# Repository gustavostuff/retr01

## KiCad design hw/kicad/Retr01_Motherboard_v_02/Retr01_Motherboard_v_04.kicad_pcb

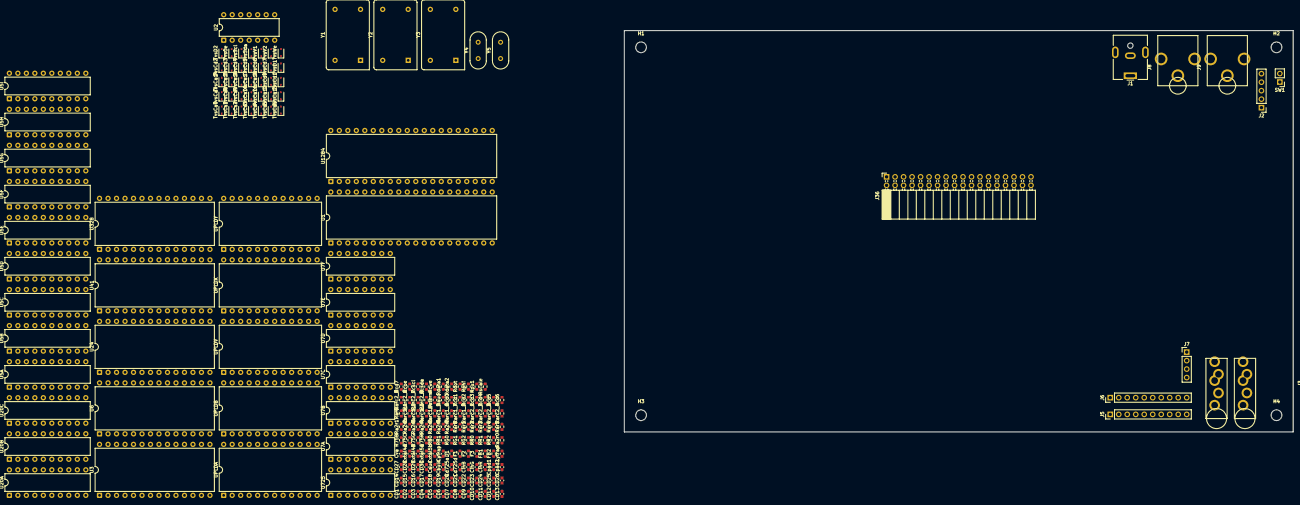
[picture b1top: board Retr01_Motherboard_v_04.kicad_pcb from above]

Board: 4 copper layers, 200.0 x 120.0 mm, 202 parts (0 on the bottom side), 213 nets, no tracks yet.

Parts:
CD1, CD2, CD3, CD4, CD5, CD6, CD7, CD8, CD9, CD10, CD11, CD12, CD13, CD14, CD15, CD16, CD17, CD18, CD19, CD20, CD21, CD22, CD23, CD24, CD25, CD26, CD27, CD28, CD29, CD30: C_100N; C_0603_1608Metric
Caud: C_10U_AUD; C_0603_1608Metric
Cbulk: C_BULK; C_0603_1608Metric
Cd725a, Cd725d: C_100N; C_0603_1608Metric
CinB: C_100N; C_0603_1608Metric
CinG: C_100N; C_0603_1608Metric
CinR: C_100N; C_0603_1608Metric
Cpad1, Cpad2: C_100N; C_0603_1608Metric
Cva: C_10U; C_0603_1608Metric
Cxtal4a, Cxtal4b, Cxtal5a, Cxtal5b: C_22P; C_0603_1608Metric
Cytrap: C_100N; C_0603_1608Metric
D1: SCHOTTKY; R_0603_1608Metric
F1, F2, F3: PPTC; R_0603_1608Metric
FB1, FB2: FERRITE; R_0603_1608Metric
H1, H2, H3, H4: MountingHole_3.2mm_M3
J1: BARREL_5V; BarrelJack_CUI_PJ-063AH_Horizontal
J2: RGBS_HDR; PinHeader_1x05_P2.54mm_Vertical
J3: TRS_P1; Jack_3.5mm_Switchcraft_35RAPC2BVN4_Vertical
J4: TRS_P2; Jack_3.5mm_Switchcraft_35RAPC2BVN4_Vertical
J5: ARCADE_P1; PinHeader_1x10_P2.54mm_Vertical
J6: ARCADE_P2; PinHeader_1x10_P2.54mm_Vertical
J7: CAB_PWR_RST; PinHeader_1x04_P2.54mm_Vertical
J8: AUDIO_OUT; CUI_RCJ-01x_Vertical
J9: COMPOSITE_OUT; CUI_RCJ-01x_Vertical
J36: CART_EDGE_36; PinSocket_2x18_P2.54mm_Horizontal
Lytrap: L_YTRAP; L_0603_1608Metric
R75B, R75C, R75G, R75R: R_75; R_0603_1608Metric
RB0: R_2K; R_0603_1608Metric
RB1: R_1K; R_0603_1608Metric
RG0: R_4K; R_0603_1608Metric
RG1: R_2K; R_0603_1608Metric
RG2: R_1K; R_0603_1608Metric
RR0: R_4K; R_0603_1608Metric
RR1: R_2K; R_0603_1608Metric
RR2: R_1K; R_0603_1608Metric
Ra2r0, Ra2r1, Ra2r2, Ra2r3, Ra2r4, Ra2r5, Ra2r6, Ra2r7: R_20K; R_0603_1608Metric
Rar0, Rar1, Rar2, Rar3, Rar4, Rar5, Rar6: R_10K; R_0603_1608Metric
Rarc1_1, Rarc1_2, Rarc1_3, Rarc1_4, Rarc1_5, Rarc1_6, Rarc1_7, Rarc1_8, Rarc2_1, Rarc2_2, Rarc2_3, Rarc2_4, Rarc2_5, Rarc2_6, Rarc2_7, Rarc2_8: R_47; R_0603_1608Metric
Raterm: R_20K; R_0603_1608Metric
Raud: R_1K; R_0603_1608Metric
Rcd0, Rcd1, Rcd2, Rcd3, Rcd4, Rcd5, Rcd6, Rcd7: R_33; R_0603_1608Metric
Rcoe: R_33; R_0603_1608Metric
Rcscl: R_33; R_0603_1608Metric
Rcsda: R_33; R_0603_1608Metric
Rcwe: R_33; R_0603_1608Metric
Rdata1, Rdata2: R_47; R_0603_1608Metric
Rdot: R_33; R_0603_1608Metric
Rphi: R_33; R_0603_1608Metric
Rpu1: R_4K7; R_0603_1608Metric
Rscale: R_10K; R_0603_1608Metric
SW1: SCALE_SW; PinHeader_1x02_P2.54mm_Vertical
TvsCa0, TvsCa1, TvsCa2, TvsCa3, TvsCa4, TvsCa5, TvsCa6, TvsCa7, TvsCa8, TvsCa9, TvsCa10, TvsCa11, TvsCa12, TvsCa13, TvsCa14, TvsCa15, TvsCa16, TvsCa17, TvsCa18: TVS_5V; D_SOD-323
TvsCd0, TvsCd1, TvsCd2, TvsCd3, TvsCd4, TvsCd5, TvsCd6, TvsCd7: TVS_5V; D_SOD-323
TvsD1, TvsD2: TVS_5V; D_SOD-323
TvsOe: TVS_5V; D_SOD-323
TvsScl: TVS_5V; D_SOD-323
TvsSda: TVS_5V; D_SOD-323
TvsV1, TvsV2: TVS_5V; D_SOD-323
TvsWe: TVS_5V; D_SOD-323
U1: W65C02S; DIP-40_W15.24mm
U2: SN74HC14; DIP-14_W7.62mm
U3, U6, U41: AS6C62256; DIP-28_W15.24mm
U5A, U5B, U5C, U5D, U5E, U5F, U5G, U5H, U5I: SN74HC573; DIP-20_W7.62mm
U7A, U7B, U7C, U7D, U7E, U7F: SN74HC157; DIP-16_W7.62mm
U20A, U20B, U20C: SN74HC245; DIP-20_W7.62mm
U24: AT27C256R; DIP-28_W15.24mm
U328: ATmega328P; DIP-28_W15.24mm
U725: AD725; DIP-16_W7.62mm
U1284: ATmega1284P; DIP-40_W15.24mm
UPLDA: ATF22V10; DIP-24_W15.24mm
UPLDB: ATF22V10; DIP-24_W15.24mm
UPLDV: ATF22V10; DIP-24_W15.24mm
UPLDX: ATF22V10; DIP-24_W15.24mm
UPLDY: ATF22V10; DIP-24_W15.24mm
Y1: OSC8M; Oscillator_DIP-14
Y2: OSC_DOT; Oscillator_DIP-14
Y3: OSC_4FSC; Oscillator_DIP-14
Y4: XTAL_20M; Crystal_HC49-U_Vertical
Y5: XTAL_16M; Crystal_HC49-U_Vertical

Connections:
+5V: CD1.1, CD2.1, CD3.1, CD4.1, CD5.1, CD6.1, CD7.1, CD8.1, CD9.1, CD10.1, CD11.1, CD12.1, CD13.1, CD14.1, CD15.1, CD16.1, CD17.1, CD18.1, CD19.1, CD20.1, CD21.1, CD22.1, CD23.1, CD24.1, CD25.1, CD26.1, CD27.1, CD28.1, CD29.1, CD30.1, Cbulk.1, Cd725a.1, Cd725d.1, Cva.1, F2.1, F3.1, FB1.2, FB2.1, FB2.2, J7.1, J36.2, J36.20, Rpu1.1, SW1.2, U1.8, U2.14, U3.28, U5A.20, U5B.20, U5C.20, U5D.20, U5E.20, U5F.20, U5G.20, U5H.20, U5I.20, U6.28, U7A.16, U7B.16, U7C.16, U7D.16, U7E.16, U7F.16, U20A.20, U20B.20, U20C.20, U24.28, U41.28, U328.7, U725.1, U725.4, U725.5, U725.14, U725.15, U1284.10, UPLDA.24, UPLDB.24, UPLDV.24, UPLDX.24, UPLDY.24, Y1.1, Y1.14, Y2.1, Y2.14, Y3.1, Y3.14
AD725_BIN: CinB.2, U725.8
AD725_GIN: CinG.2, U725.7
AD725_RIN: CinR.2, U725.6
ASUM0: Ra2r0.2, Rar0.1, Raterm.1
ASUM1: Ra2r1.2, Rar0.2, Rar1.1
ASUM2: Ra2r2.2, Rar1.2, Rar2.1
ASUM3: Ra2r3.2, Rar2.2, Rar3.1
ASUM4: Ra2r4.2, Rar3.2, Rar4.1
ASUM5: Ra2r5.2, Rar4.2, Rar5.1
ASUM6: Ra2r6.2, Rar5.2, Rar6.1
AUD0: Ra2r0.1, U328.14
AUD1: Ra2r1.1, U328.15
AUD2: Ra2r2.1, U328.16
AUD3: Ra2r3.1, U328.17
AUD4: Ra2r4.1, U328.18
AUD5: Ra2r5.1, U328.19
AUD6: Ra2r6.1, U328.23
AUD7: Ra2r7.1, U328.24
AUDIO_OUT: Caud.2, J8.1
AUDIO_SUM: Caud.1, Ra2r7.2, Rar6.2, Raud.1
BEAM_LB_A9: U7D.6, U7E.6, U7F.6, UPLDX.16, UPLDY.3
BEAM_LB_A10: U7D.10, U7E.10, U7F.10, UPLDX.17, UPLDY.4
BEAM_LB_A11: U7D.13, U7E.13, U7F.13, UPLDX.18, UPLDY.5
BEAM_Y0: U7D.3, U7E.3, U7F.3, UPLDX.15, UPLDY.2
BEAM_Y4: UPLDX.19, UPLDY.6
BEAM_Y5: UPLDX.20, UPLDY.7
BEAM_Y6: UPLDX.21, UPLDY.8
BEAM_Y7: UPLDX.22, UPLDY.9
CART_A0: J36.4, TvsCa0.1, U1.9, U3.10, UPLDA.2
CART_A5: J36.9, TvsCa5.1, U1.14, U3.5, UPLDA.7
CART_A6: J36.10, TvsCa6.1, U1.15, U3.4, UPLDA.8
CART_A7: J36.11, TvsCa7.1, U1.16, U3.3, UPLDA.9
CART_A8: J36.12, TvsCa8.1, U1.17, U3.25
CART_A11: J36.15, TvsCa11.1, U1.20, U3.23
CART_A13: J36.17, TvsCa13.1, U1.23, U3.26
CART_A14: J36.31, TvsCa14.1, U5G.19
CART_A15: J36.32, TvsCa15.1, U5H.18
CART_A16: J36.33, TvsCa16.1, U5I.17
CART_A17: J36.34, TvsCa17.1, U5I.16
CART_A18: J36.35, TvsCa18.1, U5I.15
CART_D0: J36.22, Rcd0.2, TvsCd0.1
CART_D0_MCU: Rcd0.1, U20C.18
CART_D1: J36.23, Rcd1.2, TvsCd1.1
CART_D1_MCU: Rcd1.1, U20C.17
CART_D2: J36.24, Rcd2.2, TvsCd2.1
CART_D2_MCU: Rcd2.1, U20C.16
CART_D3: J36.25, Rcd3.2, TvsCd3.1
CART_D3_MCU: Rcd3.1, U20C.15
CART_D4: J36.26, Rcd4.2, TvsCd4.1
CART_D4_MCU: Rcd4.1, U20C.14
CART_D5: J36.27, Rcd5.2, TvsCd5.1
CART_D5_MCU: Rcd5.1, U20C.13
CART_D6: J36.28, Rcd6.2, TvsCd6.1
CART_D6_MCU: Rcd6.1, U20C.12
CART_D7: J36.29, Rcd7.2, TvsCd7.1
CART_D7_MCU: Rcd7.1, U20C.11
CART_OE_MCU: Rcoe.1, UPLDB.20
CART_OE_N: J36.30, Rcoe.2, TvsOe.1
CART_WE_MCU: Rcwe.1, UPLDB.21
CART_WE_N: J36.36, Rcwe.2, TvsWe.1
COMPOSITE_OUT: J9.1, R75C.2
COMP_RAW: R75C.1, U725.10
CPU_A9: J36.13, TvsCa9.1, U1.18, U3.24
CPU_A10: J36.14, TvsCa10.1, U1.19, U3.21
CPU_A12: J36.16, TvsCa12.1, U1.22, U3.2
CPU_A14: U1.24, U3.1
CPU_A_LO1: J36.5, TvsCa1.1, U1.10, U3.9, UPLDA.3
CPU_A_LO2: J36.6, TvsCa2.1, U1.11, U3.8, UPLDA.4
CPU_A_LO3: J36.7, TvsCa3.1, U1.12, U3.7, UPLDA.5
CPU_A_LO4: J36.8, TvsCa4.1, U1.13, U3.6, UPLDA.6
CPU_BE: U1.36, UPLDA.10
CPU_D0: U1.33, U3.11, U5A.2, U5B.2, U5C.2, U5D.2, U5E.2, U5F.2, U5G.2, U5H.2, U5I.2, U6.11, U7A.2, U7A.3, U20A.2, U20A.18, U20C.2, U328.2, U1284.24, UPLDB.2
CPU_D3: U1.30, U3.15, U5A.5, U5B.5, U5C.5, U5D.5, U5E.5, U5F.5, U5G.5, U5H.5, U5I.5, U6.15, U7A.13, U7A.14, U20A.5, U20A.15, U20C.5, U328.5, U1284.27, UPLDB.5
CPU_D4: U1.29, U3.16, U5A.6, U5B.6, U5C.6, U5D.6, U5E.6, U5F.6, U5G.6, U5H.6, U5I.6, U6.16, U7B.2, U7B.3, U20A.6, U20A.14, U20C.6, U328.6, U1284.28, UPLDB.6
CPU_RWB: U1.34, UPLDA.11
CPU_VA2: U1.31, U3.13, U5A.4, U5B.4, U5C.4, U5D.4, U5E.4, U5F.4, U5G.4, U5H.4, U5I.4, U6.13, U7A.10, U7A.11, U20A.4, U20A.16, U20C.4, U328.4, U1284.26, UPLDB.4
CPU_VA6: U1.27, U3.18, U5A.8, U5B.8, U5C.8, U5D.8, U5E.8, U5F.8, U5G.8, U5H.8, U5I.8, U6.18, U7B.10, U7B.11, U20A.8, U20A.12, U20C.8, U328.12, U1284.20, UPLDB.8
CPU_VA8: U7C.2, U7C.3, UPLDB.10
CSYNC: J2.4, U725.16, UPLDV.14
DIR_CART245: U20C.1, UPLDB.18
DIR_CPU245: U7C.13, U7C.14, U20A.1, UPLDB.14
DIR_VID245: U6.26, U20B.1, UPLDB.16
DOT_CLK: Rdot.2, UPLDX.1
DOT_SRC: Rdot.1, Y2.8
FSC4: U725.3, Y3.8
GND: CD1.2, CD2.2, CD3.2, CD4.2, CD5.2, CD6.2, CD7.2, CD8.2, CD9.2, CD10.2, CD11.2, CD12.2, CD13.2, CD14.2, CD15.2, CD16.2, CD17.2, CD18.2, CD19.2, CD20.2, CD21.2, CD22.2, CD23.2, CD24.2, CD25.2, CD26.2, CD27.2, CD28.2, CD29.2, CD30.2, Cbulk.2, Cd725a.2, Cd725d.2, Cpad1.2, Cpad2.2, Cva.2, Cxtal4a.2, Cxtal4b.2, Cxtal5a.2, Cxtal5b.2, Cytrap.2, J1.2, J1.MP, J2.5, J3.1, J4.1, J5.9, J5.10, J6.9, J6.10, J7.2, J7.4, J8.2, J9.2, J36.1, J36.18, J36.19, R75B.2, R75G.2, R75R.2, Raterm.2, Rscale.2, TvsCa0.2, TvsCa1.2, TvsCa2.2, TvsCa3.2, TvsCa4.2, TvsCa5.2, TvsCa6.2, TvsCa7.2, TvsCa8.2, TvsCa9.2, TvsCa10.2, TvsCa11.2, TvsCa12.2, TvsCa13.2, TvsCa14.2, TvsCa15.2, TvsCa16.2, TvsCa17.2, TvsCa18.2, TvsCd0.2, TvsCd1.2, TvsCd2.2, TvsCd3.2, TvsCd4.2, TvsCd5.2, TvsCd6.2, TvsCd7.2, TvsD1.2, TvsD2.2, TvsOe.2, TvsScl.2, TvsSda.2, TvsV1.2, TvsV2.2, TvsWe.2, U1.21, U3.14, U5A.10, U5B.10, U5C.10, U5D.10, U5E.10, U5F.10, U5G.10, U5H.10, U5I.10, U6.14, U7A.8, U7B.8, U7C.8, U7D.8, U7E.8, U7F.8, U20A.10, U20B.10, U20C.10, U24.14, U41.14, U328.8, U725.2, U725.13, U1284.11, UPLDA.12, UPLDB.12, UPLDV.12, UPLDX.12, UPLDY.12, Y1.7, Y2.7, Y3.7
I2C_SCL: J36.21, Rcscl.2, TvsScl.1
I2C_SCL_MCU: Rcscl.1, U1284.22
I2C_SDA: J36.3, Rcsda.2, TvsSda.1
I2C_SDA_MCU: Rcsda.1, U1284.23
IRQ_N: U1.4, UPLDY.22
LB_A0: U7D.4, U41.10
LB_A1: U7D.7, U41.9
LB_A2: U7D.9, U41.8
LB_A3: U7D.12, U41.7
LB_A4: U7E.4, U41.6
LB_A5: U7E.7, U41.5
LB_A6: U7E.9, U41.4
LB_A7: U7E.12, U41.3
LB_A8: U7F.4, U41.25
LB_A9: U7F.7, U41.24
LB_A10: U7F.9, U41.21
LB_A11: U7F.12, U41.23
LB_MUX_AB: U7D.1, U7E.1, U7F.1, U1284.17
LB_MUX_G_N: U7D.15, U7E.15, U7F.15
MCU_LB_A0: Rarc2_1.2, U7D.2, U7F.2, U1284.1
MCU_LB_A2: Rarc2_3.2, U7D.11, U7F.11, U1284.3
MCU_LB_A4: Rarc2_5.2, U7E.2, U41.2, U1284.5
MUX_G_N: U7A.15, U7B.15, U7C.15
NMI_N: U1.6, UPLDX.14
OE_CART245: U20C.19, UPLDB.19
OE_CPU245: U6.2, U20A.19, UPLDB.15
OE_VID245: U6.1, U20B.19, UPLDB.17
P1_COIN: Rarc1_7.2, U1284.34
P1_COIN_J: J5.7, Rarc1_7.1
P1_DOWN: Rarc1_3.2, U1284.38
P1_DOWN_J: J5.3, Rarc1_3.1
P1_LEFT: Rarc1_2.2, U1284.39
P1_LEFT_J: J5.2, Rarc1_2.1
P1_RIGHT: Rarc1_1.2, U1284.40
P1_RIGHT_J: J5.1, Rarc1_1.1
P1_START: Rarc1_8.2, U1284.33
P1_START_J: J5.8, Rarc1_8.1
P1_UP: Rarc1_4.2, U1284.37
P1_UP_J: J5.4, Rarc1_4.1
P1_X: Rarc1_5.2, U1284.36
P1_X_J: J5.5, Rarc1_5.1
P1_Y: Rarc1_6.2, U1284.35
P1_Y_J: J5.6, Rarc1_6.1
P2_COIN: Rarc2_7.2, U7E.11, U41.1, U1284.7
P2_COIN_J: J6.7, Rarc2_7.1
P2_DOWN_J: J6.3, Rarc2_3.1
P2_LEFT: Rarc2_2.2, U7D.5, U7F.5, U1284.2
P2_LEFT_J: J6.2, Rarc2_2.1
P2_RIGHT_J: J6.1, Rarc2_1.1
P2_START: Rarc2_8.2, U7E.14, U1284.8
P2_START_J: J6.8, Rarc2_8.1
P2_UP: Rarc2_4.2, U7D.14, U7F.14, U1284.4
P2_UP_J: J6.4, Rarc2_4.1
P2_X_J: J6.5, Rarc2_5.1
P2_Y: Rarc2_6.2, U7E.5, U41.26, U1284.6
P2_Y_J: J6.6, Rarc2_6.1
PAD_DATA: Rdata1.1, Rdata2.1, Rpu1.2, U1284.16
PAD_DATA_P1: J3.2, Rdata1.2, TvsD1.1
PAD_DATA_P2: J4.2, Rdata2.2, TvsD2.1
PAD_VCC_P1: Cpad1.1, F2.2, J3.4, TvsV1.1
PAD_VCC_P2: Cpad2.1, F3.2, J4.4, TvsV2.1
PHI2: Rphi.2, U1.37, U2.1, U2.2, U7A.1, U7B.1, U7C.1
PHI2_SRC: Rphi.1, Y1.8
PPU_VA1: U1.32, U3.12, U5A.3, U5B.3, U5C.3, U5D.3, U5E.3, U5F.3, U5G.3, U5H.3, U5I.3, U6.12, U7A.5, U7A.6, U20A.3, U20A.17, U20C.3, U328.3, U1284.25, UPLDB.3
PPU_VA5: U1.28, U3.17, U5A.7, U5B.7, U5C.7, U5D.7, U5E.7, U5F.7, U5G.7, U5H.7, U5I.7, U6.17, U7B.5, U7B.6, U20A.7, U20A.13, U20C.7, U328.11, U1284.29, UPLDB.7
PPU_VA7: U1.26, U3.19, U5A.9, U5B.9, U5C.9, U5D.9, U5E.9, U5F.9, U5G.9, U5H.9, U5I.9, U6.19, U7B.13, U7B.14, U20A.9, U20A.11, U20C.9, U328.13, U1284.21, UPLDB.9
PPU_VA9: U7C.5, U7C.6, UPLDB.11
PPU_VA10: U7C.10, U7C.11, UPLDB.13
PROM_A0: U24.10, UPLDV.2
PROM_A1: U24.9, UPLDV.3
PROM_A2: U24.8, UPLDV.4
PROM_A3: U24.7, UPLDV.5
PROM_A4: U24.6, UPLDV.6
PROM_A5: U24.5, UPLDV.7
PROM_D0: RB0.1, U24.11
PROM_D1: RB1.1, U24.12
PROM_D2: RG0.1, U24.13
PROM_D3: RG1.1, U24.15
PROM_D4: RG2.1, U24.16
PROM_D5: RR0.1, U24.17
PROM_D6: RR1.1, U24.18
PROM_D7: RR2.1, U24.19
RASTER_Y0: U5D.19, UPLDY.14
RASTER_Y1: U5D.18, UPLDY.15
RASTER_Y2: U5D.17, UPLDY.16
RASTER_Y3: U5D.16, UPLDY.17
RASTER_Y4: U5D.15, UPLDY.18
RASTER_Y5: U5D.14, UPLDY.19
RASTER_Y6: U5D.13, UPLDY.20
RASTER_Y7: U5D.12, UPLDY.21
RESET_N: J7.3, U1.40, U2.3, UPLDX.13
SCALE_1X: Rscale.1, SW1.1, UPLDV.13
SEL_FE02: U5B.11, U1284.19, UPLDA.15
SEL_FE03: U5C.11, UPLDA.16
SEL_FE04: U5D.11, UPLDA.17
SEL_FE05: U5E.11, UPLDA.18
SEL_FE06: U5A.11, U1284.18, UPLDA.14
SEL_FE08: U5F.11, UPLDA.19
SEL_FE11: UPLDA.23, UPLDB.22, UPLDB.23
SEL_FE90: U5G.11, UPLDA.20
SEL_FE91: U5H.11, UPLDA.21
SEL_FE92: U5I.11, UPLDA.22
VIDEO_B: CinB.1, J2.3, R75B.1, RB0.2, RB1.2
VIDEO_G: CinG.1, J2.2, R75G.1, RG0.2, RG1.2, RG2.2
VIDEO_R: CinR.1, J2.1, R75R.1, RR0.2, RR1.2, RR2.2
VIN_FUSED: F1.2, FB1.1
VIN_PROT: D1.2, F1.1
VIN_RAW: D1.1, J1.1
VRAM_A0: U6.10, U7A.4
VRAM_A1: U6.9, U7A.7
VRAM_A2: U6.8, U7A.9
VRAM_A3: U6.7, U7A.12
VRAM_A4: U6.6, U7B.4
VRAM_A5: U6.5, U7B.7
VRAM_A6: U6.4, U7B.9
VRAM_A7: U6.3, U7B.12
VRAM_A8: U6.25, U7C.4
VRAM_A9: U6.24, U7C.7
VRAM_A10: U6.21, U7C.9
VRAM_A11: U6.23, U7C.12
XTAL328: Cxtal5a.1, U328.9, Y5.1
XTAL328b: Cxtal5b.1, U328.10, Y5.2
XTAL1284: Cxtal4a.1, U1284.13, Y4.1
XTAL1284b: Cxtal4b.1, U1284.12, Y4.2
YTRAP: Lytrap.1, U725.12
YTRAP_MID: Cytrap.1, Lytrap.2

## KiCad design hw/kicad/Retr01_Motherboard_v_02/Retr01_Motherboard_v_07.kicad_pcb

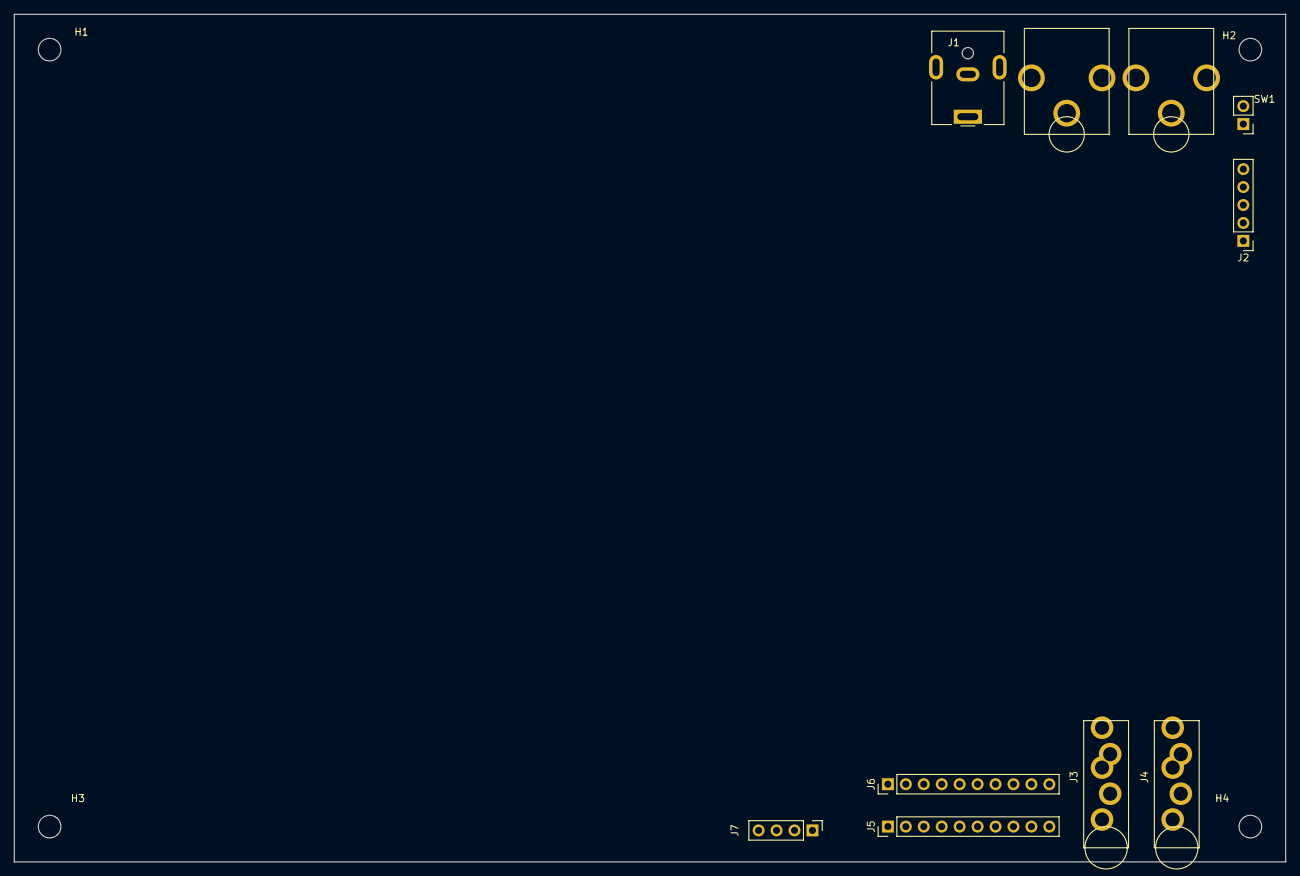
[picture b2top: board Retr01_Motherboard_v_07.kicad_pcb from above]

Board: 4 copper layers, 180.0 x 120.0 mm, 14 parts (0 on the bottom side), 2 nets, no tracks yet.

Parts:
H1, H2, H3, H4: MountingHole_3.2mm_M3
J1: BARREL_5V; BarrelJack_CUI_PJ-063AH_Horizontal
J2: RGBS_HDR; PinHeader_1x05_P2.54mm_Vertical
J3: TRS_P1; Jack_3.5mm_Switchcraft_35RAPC2BVN4_Vertical
J4: TRS_P2; Jack_3.5mm_Switchcraft_35RAPC2BVN4_Vertical
J5: ARCADE_P1; PinHeader_1x10_P2.54mm_Vertical
J6: ARCADE_P2; PinHeader_1x10_P2.54mm_Vertical
J7: CAB_PWR_RST; PinHeader_1x04_P2.54mm_Vertical
J8: AUDIO_OUT; CUI_RCJ-01x_Vertical
J9: COMPOSITE; CUI_RCJ-01x_Vertical
SW1: SCALE_SW; PinHeader_1x02_P2.54mm_Vertical

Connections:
+5V: J7.1, SW1.2
GND: J1.2, J1.MP, J2.5, J3.1, J4.1, J5.9, J5.10, J6.9, J6.10, J7.2, J7.4, J8.2, J9.2

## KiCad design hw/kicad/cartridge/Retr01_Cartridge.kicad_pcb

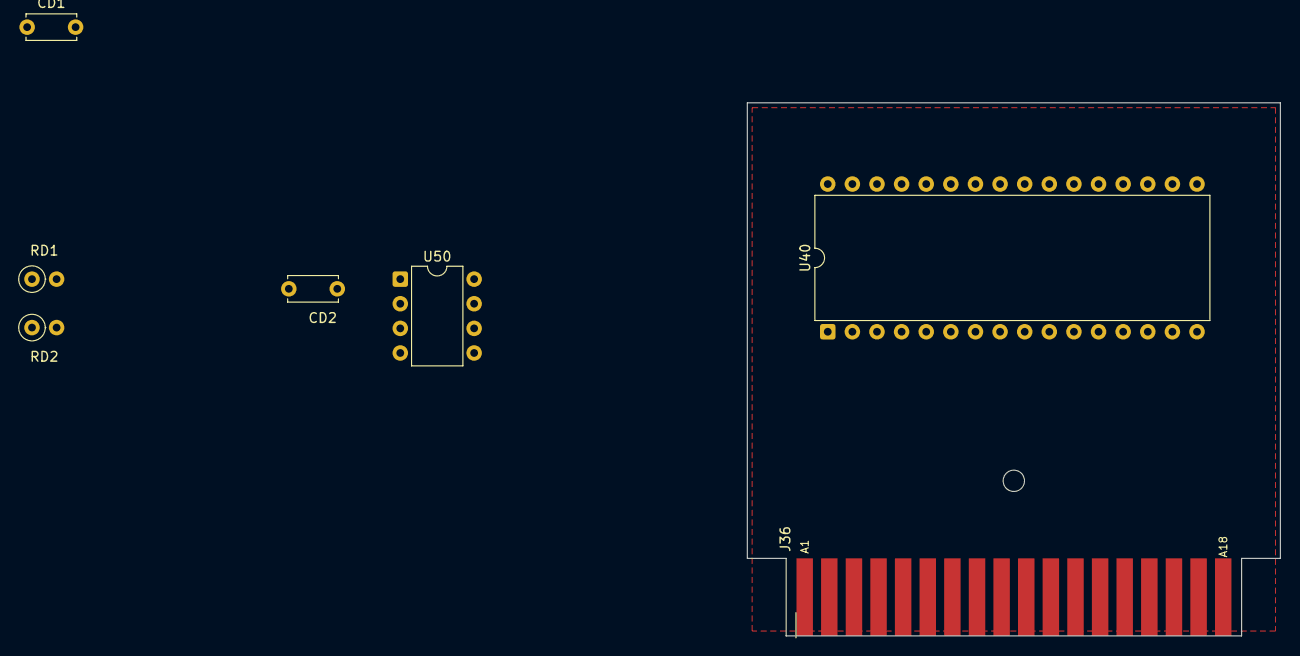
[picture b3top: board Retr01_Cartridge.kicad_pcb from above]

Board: 4 copper layers, 55.0 x 55.0 mm, 8 parts (0 on the bottom side), 35 nets, no tracks yet.

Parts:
CD1, CD2: 100nF; C_Disc_D5.0mm_W2.5mm_P5.00mm
J36: CART_EDGE_36; Cart_Edge_2x18_P2.54mm
RD1, RD2: 0; R_Axial_DIN0207_L6.3mm_D2.5mm_P2.54mm_Vertical
Screw: MountingHole_2.2mm_M2
U40: SST39SF040; DIP-32_W15.24mm
U50: 24C64; DIP-8_W7.62mm

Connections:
+5V: J36.2, J36.20, RD1.2, RD2.2
+5V_U40: CD1.1, RD1.1, U40.32
+5V_U50: CD2.1, RD2.1, U50.8
CART_A0: J36.4, U40.12
CART_A1: J36.5, U40.11
CART_A2: J36.6, U40.10
CART_A3: J36.7, U40.9
CART_A4: J36.8, U40.8
CART_A5: J36.9, U40.7
CART_A6: J36.10, U40.6
CART_A7: J36.11, U40.5
CART_A8: J36.12, U40.27
CART_A9: J36.13, U40.26
CART_A10: J36.14, U40.23
CART_A11: J36.15, U40.25
CART_A12: J36.16, U40.4
CART_A13: J36.17, U40.28
CART_A14: J36.31, U40.29
CART_A15: J36.32, U40.3
CART_A16: J36.33, U40.2
CART_A17: J36.34, U40.30
CART_A18: J36.35, U40.1
CART_D0: J36.22, U40.13
CART_D1: J36.23, U40.14
CART_D2: J36.24, U40.15
CART_D3: J36.25, U40.17
CART_D4: J36.26, U40.18
CART_D5: J36.27, U40.19
CART_D6: J36.28, U40.20
CART_D7: J36.29, U40.21
CART_OE_N: J36.30, U40.24
CART_WE_N: J36.36, U40.31
GND: CD1.2, CD2.2, J36.1, J36.18, J36.19, U40.16, U40.22, U50.1, U50.2, U50.3, U50.4, U50.7
I2C_SCL: J36.21, U50.6
I2C_SDA: J36.3, U50.5
